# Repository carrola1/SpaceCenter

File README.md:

# Space_Center

## Lessons Learned
- Need to have GCC compiler optimization turned ON (optimize for size) for audio to work
-  tsl_user.h does not appear to be updating with Code Generation. Had to manually set Channel IOs definition (line 51)

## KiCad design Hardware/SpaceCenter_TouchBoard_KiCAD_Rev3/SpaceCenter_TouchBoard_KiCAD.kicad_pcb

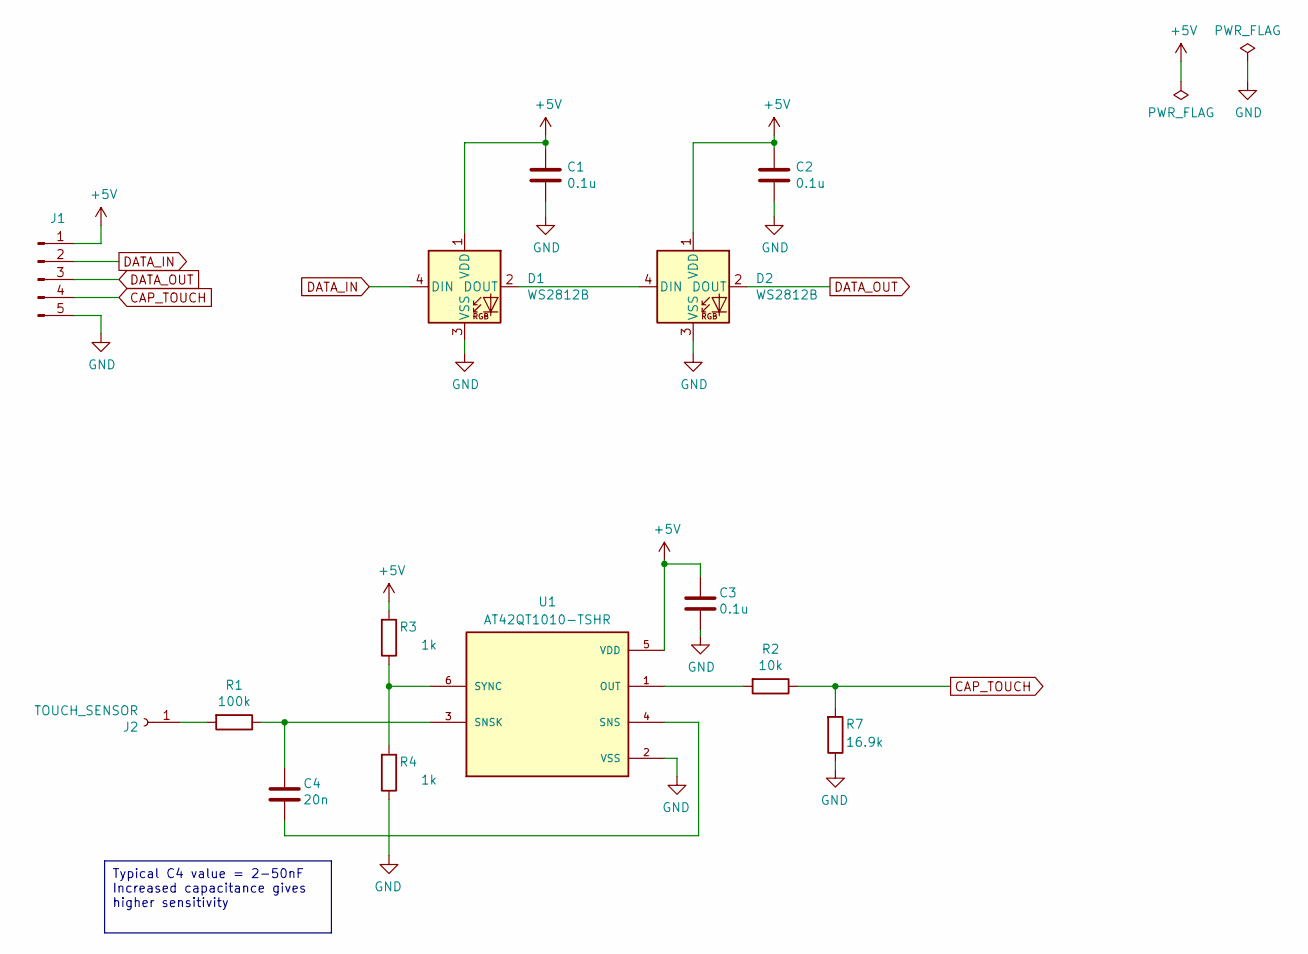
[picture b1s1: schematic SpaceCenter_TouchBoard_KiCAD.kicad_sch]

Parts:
C1, C2, C3: 0.1u; C_0402_1005Metric_Pad0.74x0.62mm_HandSolder
C4: 20n; C_0402_1005Metric_Pad0.74x0.62mm_HandSolder
D1, D2: WS2812B; LED_WS2812B_PLCC4_5.0x5.0mm_P3.2mm
J1: Conn_01x05_Male; JST_SH_BM05B-SRSS-TB_1x05-1MP_P1.00mm_Vertical
J2: TOUCH_SENSOR; SolderWirePad_1x01_SMD_5x10mm
R1: 100k; R_0402_1005Metric_Pad0.72x0.64mm_HandSolder
R2: 10k; R_0402_1005Metric_Pad0.72x0.64mm_HandSolder
R3, R4: 1k; R_0402_1005Metric_Pad0.72x0.64mm_HandSolder
R7: 16.9k; R_0402_1005Metric_Pad0.72x0.64mm_HandSolder
U1: AT42QT1010-TSHR; SOT95P270X145-6N; PARTREV DS40001946A

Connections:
+5V: C1.1, C2.1, C3.1, D1.1 (VDD), D2.1 (VDD), J1.1, R3.2, U1.5 (VDD); also elsewhere on the board
CAP_TOUCH: J1.4, R2.1, R7.2
DATA_IN: D1.4 (DIN), J1.2
DATA_OUT: D2.2 (DOUT), J1.3
GND: C1.2, C2.2, C3.2, D1.3 (VSS), D2.3 (VSS), J1.5, R4.1, R7.1, U1.2 (VSS); also elsewhere on the board
unnamed: D1.2 (DOUT), D2.4 (DIN)
unnamed: J2.1, R1.2
unnamed: R2.2, U1.1 (OUT)
unnamed: C4.2, U1.4 (SNS)
unnamed: C4.1, R1.1, U1.3 (SNSK)
unnamed: R3.1, R4.2, U1.6 (SYNC)

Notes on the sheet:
Typical C4 value = 2-50nF Increased capacitance gives higher sensitivity

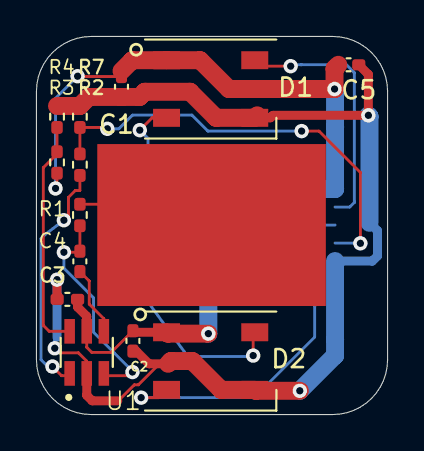
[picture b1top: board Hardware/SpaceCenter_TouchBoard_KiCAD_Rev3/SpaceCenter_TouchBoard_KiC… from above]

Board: 2 copper layers, 19.5 x 21.0 mm, 15 parts (1 on the bottom side), 11 nets.

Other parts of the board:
C5: 10u; C_0402_1005Metric_Pad0.74x0.62mm_HandSolder

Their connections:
+5V: C5.1; also elsewhere on the board
GND: C5.2; also elsewhere on the board

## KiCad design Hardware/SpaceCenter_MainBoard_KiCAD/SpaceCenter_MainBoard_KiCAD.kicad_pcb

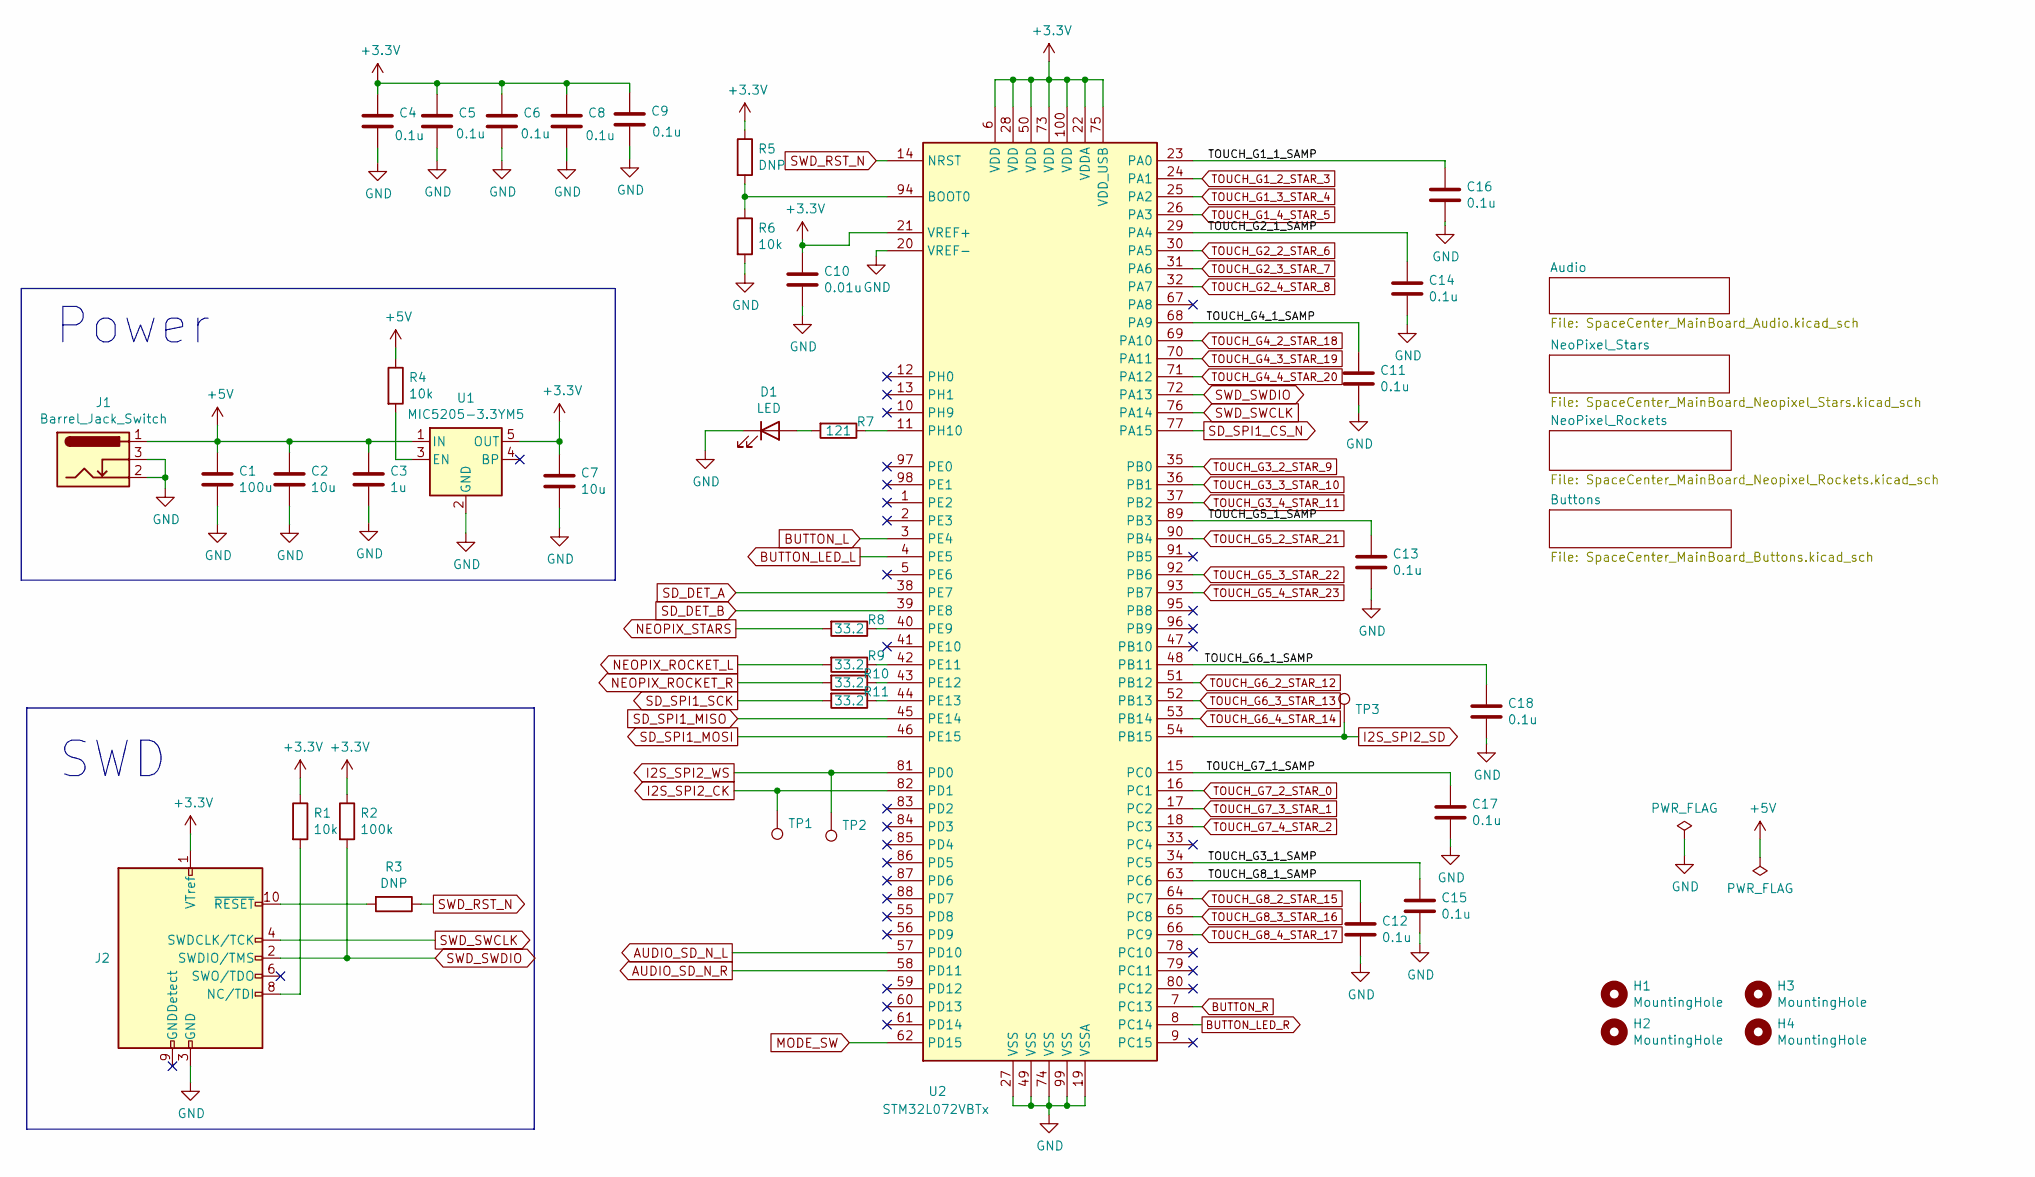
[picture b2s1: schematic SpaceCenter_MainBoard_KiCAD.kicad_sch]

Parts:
C1: 100u; C_1206_3216Metric_Pad1.42x1.75mm_HandSolder
C2, C7: 10u; C_0603_1608Metric_Pad1.05x0.95mm_HandSolder
C3: 1u; C_0603_1608Metric_Pad1.05x0.95mm_HandSolder
C4, C5, C6, C8, C9, C11, C12, C13, C14, C15, C16, C17, C18: 0.1u; C_0603_1608Metric_Pad1.05x0.95mm_HandSolder
C10: 0.01u; C_0603_1608Metric_Pad1.05x0.95mm_HandSolder
D1: LED; LED_0603_1608Metric_Pad1.05x0.95mm_HandSolder
H1, H2, H3, H4: MountingHole; MountingHole_3.2mm_M3
J1: Barrel_Jack_Switch; BarrelJack_CUI_PJ-102AH_Horizontal
J2: Conn_ARM_JTAG_SWD_10; PinHeader_2x05_P1.27mm_Vertical_SMD
R1, R4, R6: 10k; R_0603_1608Metric_Pad1.05x0.95mm_HandSolder
R2: 100k; R_0603_1608Metric_Pad1.05x0.95mm_HandSolder
R3, R5: DNP; R_0603_1608Metric_Pad1.05x0.95mm_HandSolder
R7: 121; R_0603_1608Metric_Pad1.05x0.95mm_HandSolder
R8, R9, R10, R11: 33.2; R_0603_1608Metric_Pad1.05x0.95mm_HandSolder
TP1, TP2, TP3: TestPoint; TestPoint_Keystone_5019_Minature
U1: MIC5205-3.3YM5; SOT-23-5
U2: STM32L072VBTx; LQFP-100_14x14mm_P0.5mm

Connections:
+3V3: C4.1, C5.1, C6.1, C7.1, C8.1, C9.1, C10.1, J2.1 (VTref), R1.1, R2.1, R5.1, U1.5 (OUT), U2.6 (VDD), U2.21 (VREF+), U2.22 (VDDA), U2.28 (VDD), U2.50 (VDD), U2.73 (VDD), U2.75 (VDD_USB), U2.100 (VDD); also elsewhere on the board
+5V: C1.1, C2.1, C3.1, J1.1, R4.1, U1.1 (IN); also elsewhere on the board
/TOUCH_G1_1_SAMP: C16.1, U2.23 (PA0)
/TOUCH_G2_1_SAMP: C14.1, U2.29 (PA4)
/TOUCH_G3_1_SAMP: C15.1, U2.34 (PC5)
/TOUCH_G4_1_SAMP: C11.1, U2.68 (PA9)
/TOUCH_G5_1_SAMP: C13.1, U2.89 (PB3)
/TOUCH_G6_1_SAMP: C18.1, U2.48 (PB11)
/TOUCH_G7_1_SAMP: C17.1, U2.15 (PC0)
/TOUCH_G8_1_SAMP: C12.1, U2.63 (PC6)
AUDIO_SD_N_L: U2.57 (PD10); also elsewhere on the board
AUDIO_SD_N_R: U2.58 (PD11); also elsewhere on the board
BUTTON_L: U2.3 (PE4); also elsewhere on the board
BUTTON_LED_L: U2.4 (PE5); also elsewhere on the board
BUTTON_LED_R: U2.8 (PC14); also elsewhere on the board
BUTTON_R: U2.7 (PC13); also elsewhere on the board
GND: C1.2, C2.2, C3.2, C4.2, C5.2, C6.2, C7.2, C8.2, C9.2, C10.2, C11.2, C12.2, C13.2, C14.2, C15.2, C16.2, C17.2, C18.2, D1.1 (K), J1.2, J1.3, J2.3 (GND), J2.5 (GND), R6.2, U1.2 (GND), U2.19 (VSSA), U2.20 (VREF-), U2.27 (VSS), U2.49 (VSS), U2.74 (VSS), U2.99 (VSS); also elsewhere on the board
I2S_SPI2_CK: TP1.1, U2.82 (PD1); also elsewhere on the board
I2S_SPI2_SD: TP3.1, U2.54 (PB15); also elsewhere on the board
I2S_SPI2_WS: TP2.1, U2.81 (PD0); also elsewhere on the board
MODE_SW: U2.62 (PD15); also elsewhere on the board
NEOPIX_ROCKET_L: R9.2; also elsewhere on the board
NEOPIX_ROCKET_R: R10.2; also elsewhere on the board
NEOPIX_STARS: R8.2; also elsewhere on the board
unnamed: D1.2 (A), R7.2
unnamed: J2.8 (NC/TDI), R1.2
unnamed: J2.10 (~RESET), R3.2
unnamed: R4.2, U1.3 (EN)
unnamed: R5.2, R6.1, U2.94 (BOOT0)
unnamed: R7.1, U2.11 (PH10)
unnamed: R8.1, U2.40 (PE9)
unnamed: R9.1, U2.42 (PE11)
unnamed: R10.1, U2.43 (PE12)
unnamed: R11.1, U2.44 (PE13)
SD_DET_A: U2.38 (PE7); also elsewhere on the board
SD_DET_B: U2.39 (PE8); also elsewhere on the board
SD_SPI1_CS_N: U2.77 (PA15); also elsewhere on the board
SD_SPI1_MISO: U2.45 (PE14); also elsewhere on the board
SD_SPI1_MOSI: U2.46 (PE15); also elsewhere on the board
SD_SPI1_SCK: R11.2; also elsewhere on the board
SWD_RST_N: R3.1, U2.14 (NRST)
SWD_SWCLK: J2.4 (SWDCLK/TCK), U2.76 (PA14)
SWD_SWDIO: J2.2 (SWDIO/TMS), R2.2, U2.72 (PA13)
TOUCH_G1_2_STAR_3: U2.24 (PA1); also elsewhere on the board
TOUCH_G1_3_STAR_4: U2.25 (PA2); also elsewhere on the board
TOUCH_G1_4_STAR_5: U2.26 (PA3); also elsewhere on the board
TOUCH_G2_2_STAR_6: U2.30 (PA5); also elsewhere on the board
TOUCH_G2_3_STAR_7: U2.31 (PA6); also elsewhere on the board
TOUCH_G2_4_STAR_8: U2.32 (PA7); also elsewhere on the board
TOUCH_G3_2_STAR_9: U2.35 (PB0); also elsewhere on the board
TOUCH_G3_3_STAR_10: U2.36 (PB1); also elsewhere on the board
TOUCH_G3_4_STAR_11: U2.37 (PB2); also elsewhere on the board
TOUCH_G4_2_STAR_18: U2.69 (PA10); also elsewhere on the board
TOUCH_G4_3_STAR_19: U2.70 (PA11); also elsewhere on the board
TOUCH_G4_4_STAR_20: U2.71 (PA12); also elsewhere on the board
TOUCH_G5_2_STAR_21: U2.90 (PB4); also elsewhere on the board
TOUCH_G5_3_STAR_22: U2.92 (PB6); also elsewhere on the board
TOUCH_G5_4_STAR_23: U2.93 (PB7); also elsewhere on the board
TOUCH_G6_2_STAR_12: U2.51 (PB12); also elsewhere on the board
TOUCH_G6_3_STAR_13: U2.52 (PB13); also elsewhere on the board
TOUCH_G6_4_STAR_14: U2.53 (PB14); also elsewhere on the board
TOUCH_G7_2_STAR_0: U2.16 (PC1); also elsewhere on the board
TOUCH_G7_3_STAR_1: U2.17 (PC2); also elsewhere on the board
TOUCH_G7_4_STAR_2: U2.18 (PC3); also elsewhere on the board
TOUCH_G8_2_STAR_15: U2.64 (PC7); also elsewhere on the board
TOUCH_G8_3_STAR_16: U2.65 (PC8); also elsewhere on the board
TOUCH_G8_4_STAR_17: U2.66 (PC9); also elsewhere on the board

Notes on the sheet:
Power
SWD

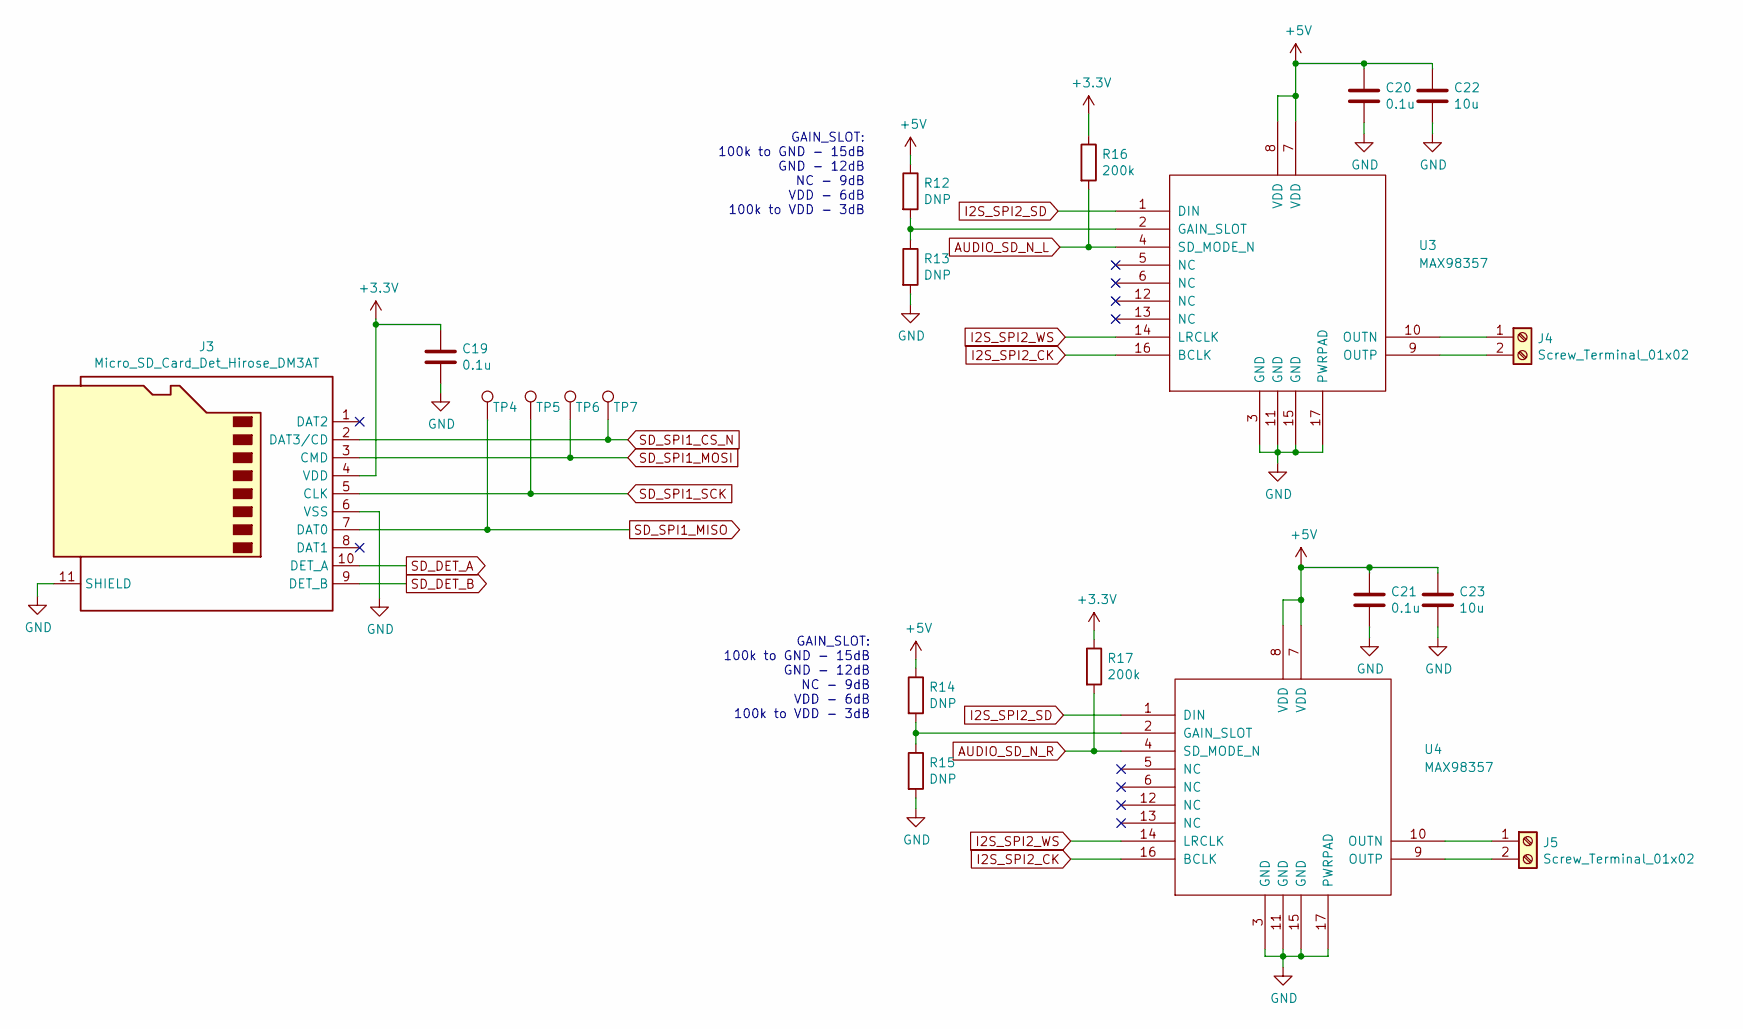
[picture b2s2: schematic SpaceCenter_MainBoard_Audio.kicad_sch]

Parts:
C19, C20, C21: 0.1u; C_0603_1608Metric_Pad1.05x0.95mm_HandSolder
C22, C23: 10u; C_0603_1608Metric_Pad1.05x0.95mm_HandSolder
J3: Micro_SD_Card_Det_Hirose_DM3AT; microSD_HC_Hirose_DM3AT-SF-PEJM5
J4, J5: Screw_Terminal_01x02; TerminalBlock_TE_282834-2_1x02_P2.54mm_Horizontal
R12, R13, R14, R15: DNP; R_0603_1608Metric_Pad1.05x0.95mm_HandSolder
R16, R17: 200k; R_0603_1608Metric_Pad1.05x0.95mm_HandSolder
TP4, TP5, TP6, TP7: TestPoint; TestPoint_Keystone_5019_Minature
U3, U4: MAX98357; QFN50P300X300X80-17N

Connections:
+3V3: C19.1, J3.4 (VDD), R16.1, R17.1; also elsewhere on the board
+5V: C20.1, C21.1, C22.1, C23.1, R12.1, R14.1, U3.7 (VDD), U3.8 (VDD), U4.7 (VDD), U4.8 (VDD); also elsewhere on the board
AUDIO_SD_N_L: R16.2, U3.4 (SD_MODE_N); also elsewhere on the board
AUDIO_SD_N_R: R17.2, U4.4 (SD_MODE_N); also elsewhere on the board
GND: C19.2, C20.2, C21.2, C22.2, C23.2, J3.6 (VSS), J3.11 (SHIELD), R13.2, R15.2, U3.3 (GND), U3.11 (GND), U3.15 (GND), U3.17 (PWRPAD), U4.3 (GND), U4.11 (GND), U4.15 (GND), U4.17 (PWRPAD); also elsewhere on the board
I2S_SPI2_CK: U3.16 (BCLK), U4.16 (BCLK); also elsewhere on the board
I2S_SPI2_SD: U3.1 (DIN), U4.1 (DIN); also elsewhere on the board
I2S_SPI2_WS: U3.14 (LRCLK), U4.14 (LRCLK); also elsewhere on the board
unnamed: J4.1, U3.10 (OUTN)
unnamed: J4.2, U3.9 (OUTP)
unnamed: J5.1, U4.10 (OUTN)
unnamed: J5.2, U4.9 (OUTP)
unnamed: R12.2, R13.1, U3.2 (GAIN_SLOT)
unnamed: R14.2, R15.1, U4.2 (GAIN_SLOT)
SD_DET_A: J3.10 (DET_A); also elsewhere on the board
SD_DET_B: J3.9 (DET_B); also elsewhere on the board
SD_SPI1_CS_N: J3.2 (DAT3/CD), TP7.1; also elsewhere on the board
SD_SPI1_MISO: J3.7 (DAT0), TP4.1; also elsewhere on the board
SD_SPI1_MOSI: J3.3 (CMD), TP6.1; also elsewhere on the board
SD_SPI1_SCK: J3.5 (CLK), TP5.1; also elsewhere on the board

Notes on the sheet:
GAIN_SLOT: 100k to GND - 15dB GND - 12dB NC - 9dB VDD - 6dB 100k to VDD - 3dB

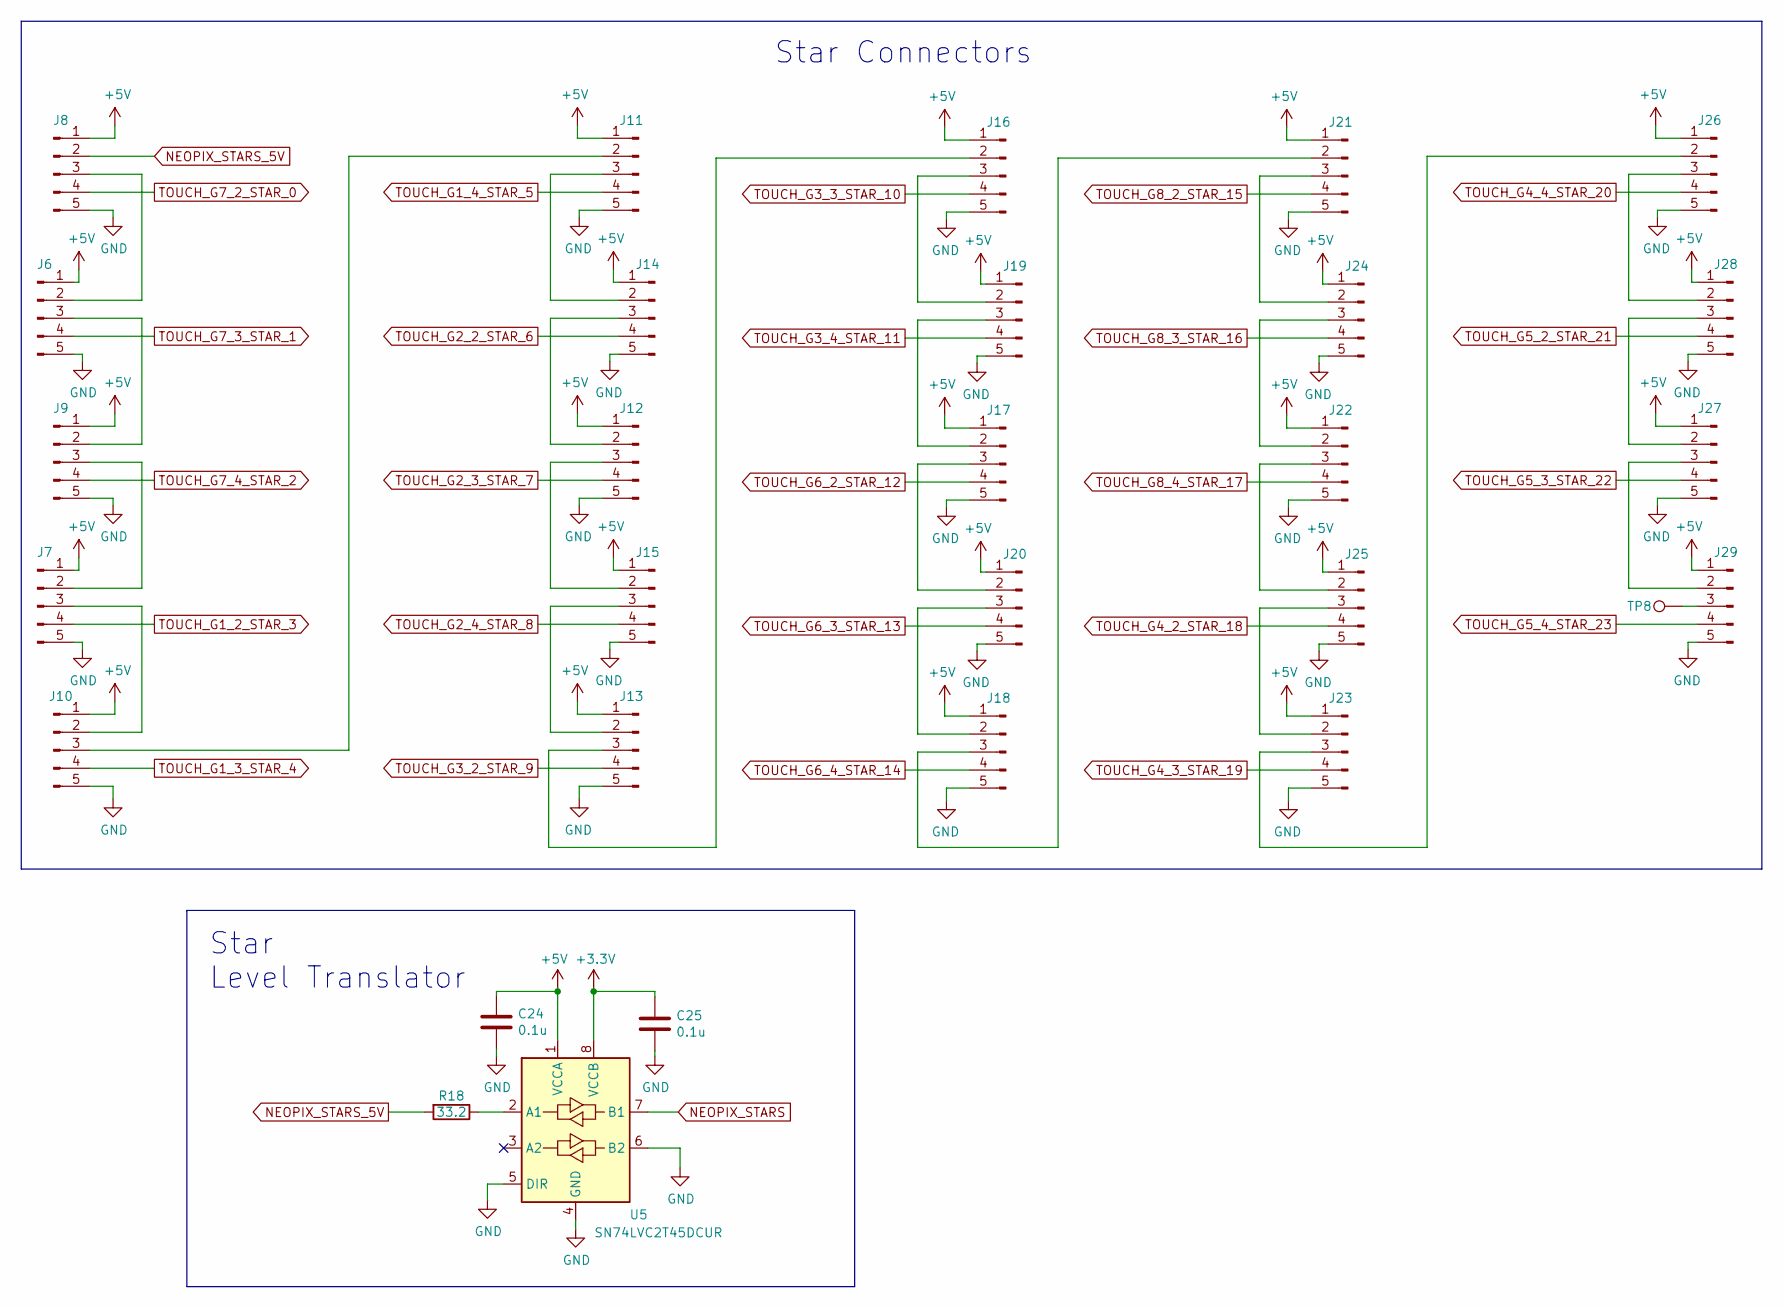
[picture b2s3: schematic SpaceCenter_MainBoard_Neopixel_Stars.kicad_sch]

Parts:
C24, C25: 0.1u; C_0603_1608Metric_Pad1.05x0.95mm_HandSolder
J6, J7, J8, J9, J10, J11, J12, J13, J14, J15, J16, J17, J18, J19, J20, J21, J22, J23, J24, J25, J26, J27, J28, J29: Conn_01x05_Male; JST_SH_BM05B-SRSS-TB_1x05-1MP_P1.00mm_Vertical
R18: 33.2; R_0603_1608Metric_Pad1.05x0.95mm_HandSolder
TP8: TestPoint; TestPoint_Keystone_5019_Minature
U5: SN74LVC2T45DCUR; VSSOP-8_2.4x2.1mm_P0.5mm

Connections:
+3V3: C25.1, U5.8 (VCCB); also elsewhere on the board
+5V: C24.1, J6.1, J7.1, J8.1, J9.1, J10.1, J11.1, J12.1, J13.1, J14.1, J15.1, J16.1, J17.1, J18.1, J19.1, J20.1, J21.1, J22.1, J23.1, J24.1, J25.1, J26.1, J27.1, J28.1, J29.1, U5.1 (VCCA); also elsewhere on the board
GND: C24.2, C25.2, J6.5, J7.5, J8.5, J9.5, J10.5, J11.5, J12.5, J13.5, J14.5, J15.5, J16.5, J17.5, J18.5, J19.5, J20.5, J21.5, J22.5, J23.5, J24.5, J25.5, J26.5, J27.5, J28.5, J29.5, U5.4 (GND), U5.5 (DIR), U5.6 (B2); also elsewhere on the board
NEOPIX_STARS: U5.7 (B1); also elsewhere on the board
NEOPIX_STARS_5V: J8.2, R18.2
unnamed: J6.2, J8.3
unnamed: J6.3, J9.2
unnamed: J7.2, J9.3
unnamed: J7.3, J10.2
unnamed: J10.3, J11.2
unnamed: J11.3, J14.2
unnamed: J12.2, J14.3
unnamed: J12.3, J15.2
unnamed: J13.2, J15.3
unnamed: J13.3, J16.2
unnamed: J16.3, J19.2
unnamed: J17.2, J19.3
unnamed: J17.3, J20.2
unnamed: J18.2, J20.3
unnamed: J18.3, J21.2
unnamed: J21.3, J24.2
unnamed: J22.2, J24.3
unnamed: J22.3, J25.2
unnamed: J23.2, J25.3
unnamed: J23.3, J26.2
unnamed: J26.3, J28.2
unnamed: J27.2, J28.3
unnamed: J27.3, J29.2
unnamed: J29.3, TP8.1
unnamed: R18.1, U5.2 (A1)
TOUCH_G1_2_STAR_3: J7.4; also elsewhere on the board
TOUCH_G1_3_STAR_4: J10.4; also elsewhere on the board
TOUCH_G1_4_STAR_5: J11.4; also elsewhere on the board
TOUCH_G2_2_STAR_6: J14.4; also elsewhere on the board
TOUCH_G2_3_STAR_7: J12.4; also elsewhere on the board
TOUCH_G2_4_STAR_8: J15.4; also elsewhere on the board
TOUCH_G3_2_STAR_9: J13.4; also elsewhere on the board
TOUCH_G3_3_STAR_10: J16.4; also elsewhere on the board
TOUCH_G3_4_STAR_11: J19.4; also elsewhere on the board
TOUCH_G4_2_STAR_18: J25.4; also elsewhere on the board
TOUCH_G4_3_STAR_19: J23.4; also elsewhere on the board
TOUCH_G4_4_STAR_20: J26.4; also elsewhere on the board
TOUCH_G5_2_STAR_21: J28.4; also elsewhere on the board
TOUCH_G5_3_STAR_22: J27.4; also elsewhere on the board
TOUCH_G5_4_STAR_23: J29.4; also elsewhere on the board
TOUCH_G6_2_STAR_12: J17.4; also elsewhere on the board
TOUCH_G6_3_STAR_13: J20.4; also elsewhere on the board
TOUCH_G6_4_STAR_14: J18.4; also elsewhere on the board
TOUCH_G7_2_STAR_0: J8.4; also elsewhere on the board
TOUCH_G7_3_STAR_1: J6.4; also elsewhere on the board
TOUCH_G7_4_STAR_2: J9.4; also elsewhere on the board
TOUCH_G8_2_STAR_15: J21.4; also elsewhere on the board
TOUCH_G8_3_STAR_16: J24.4; also elsewhere on the board
TOUCH_G8_4_STAR_17: J22.4; also elsewhere on the board

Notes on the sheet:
Star Level Translator
Star Connectors

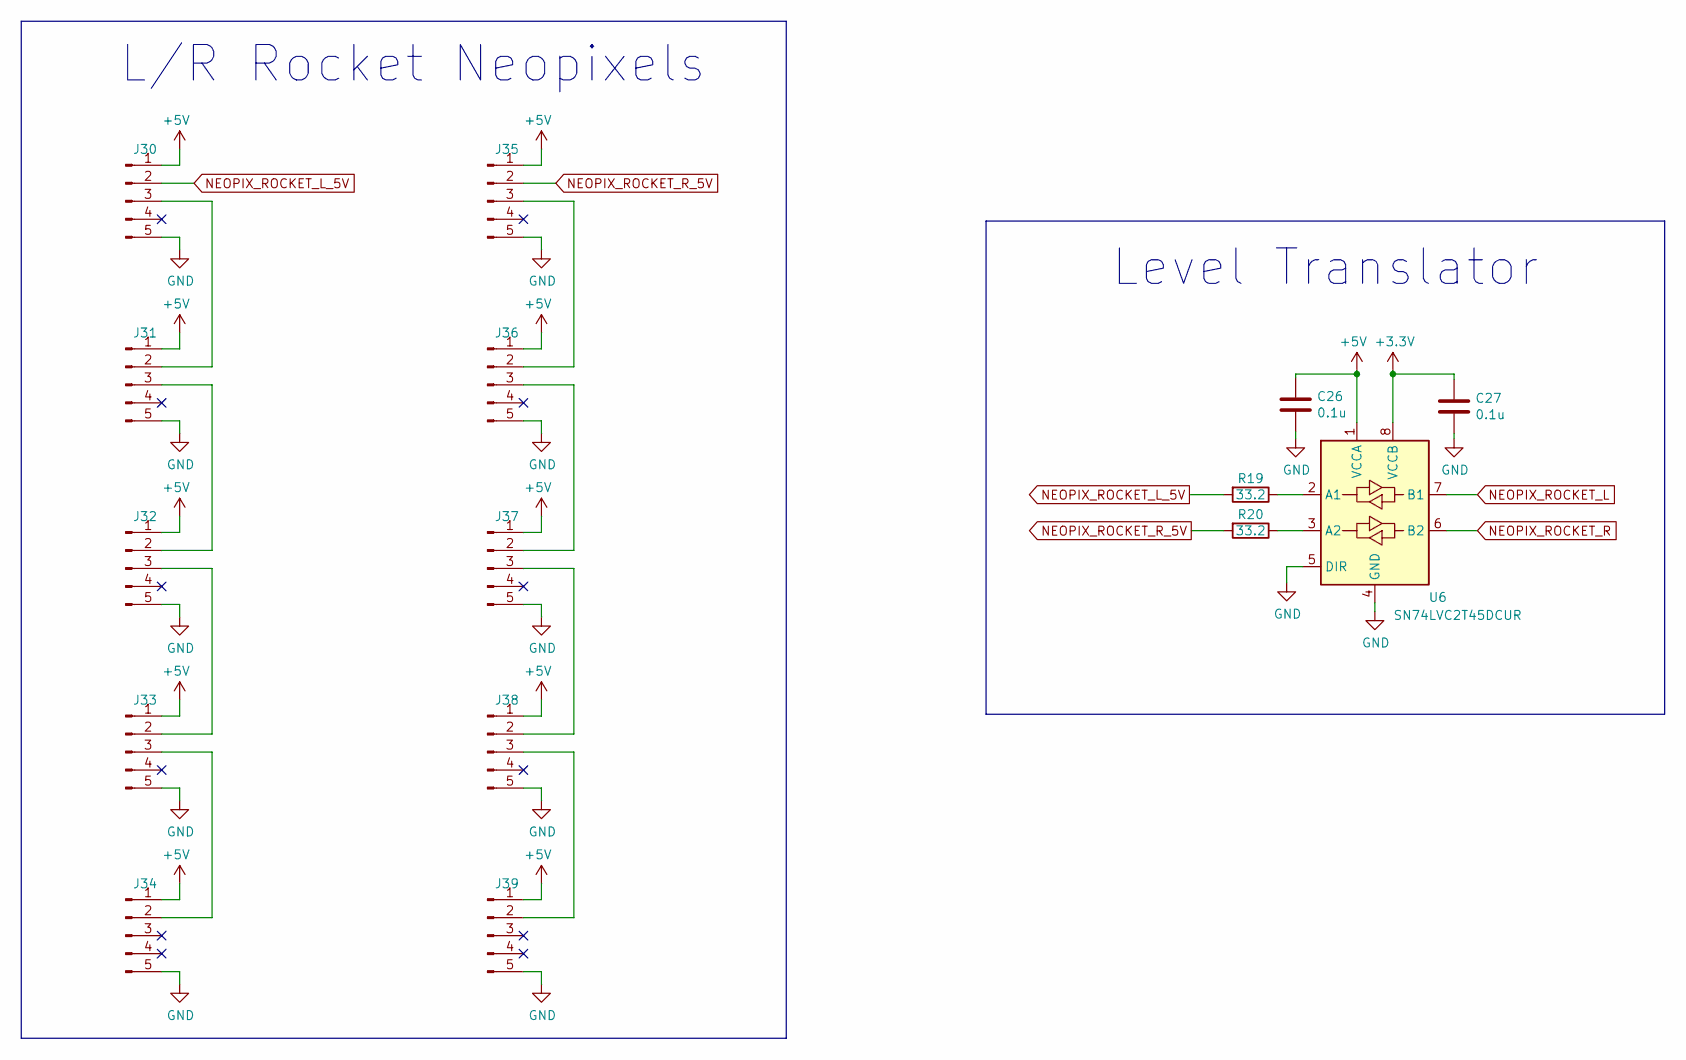
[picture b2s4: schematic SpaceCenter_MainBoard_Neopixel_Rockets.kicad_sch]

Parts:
C26, C27: 0.1u; C_0603_1608Metric_Pad1.05x0.95mm_HandSolder
J30, J31, J32, J33, J34, J35, J36, J37, J38, J39: Conn_01x05_Male; JST_SH_BM05B-SRSS-TB_1x05-1MP_P1.00mm_Vertical
R19, R20: 33.2; R_0603_1608Metric_Pad1.05x0.95mm_HandSolder
U6: SN74LVC2T45DCUR; VSSOP-8_2.4x2.1mm_P0.5mm

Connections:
+3V3: C27.1, U6.8 (VCCB); also elsewhere on the board
+5V: C26.1, J30.1, J31.1, J32.1, J33.1, J34.1, J35.1, J36.1, J37.1, J38.1, J39.1, U6.1 (VCCA); also elsewhere on the board
GND: C26.2, C27.2, J30.5, J31.5, J32.5, J33.5, J34.5, J35.5, J36.5, J37.5, J38.5, J39.5, U6.4 (GND), U6.5 (DIR); also elsewhere on the board
NEOPIX_ROCKET_L: U6.7 (B1); also elsewhere on the board
NEOPIX_ROCKET_L_5V: J30.2, R19.2
NEOPIX_ROCKET_R: U6.6 (B2); also elsewhere on the board
NEOPIX_ROCKET_R_5V: J35.2, R20.2
unnamed: J30.3, J31.2
unnamed: J31.3, J32.2
unnamed: J32.3, J33.2
unnamed: J33.3, J34.2
unnamed: J35.3, J36.2
unnamed: J36.3, J37.2
unnamed: J37.3, J38.2
unnamed: J38.3, J39.2
unnamed: R19.1, U6.2 (A1)
unnamed: R20.1, U6.3 (A2)

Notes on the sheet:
Level Translator
L/R Rocket Neopixels

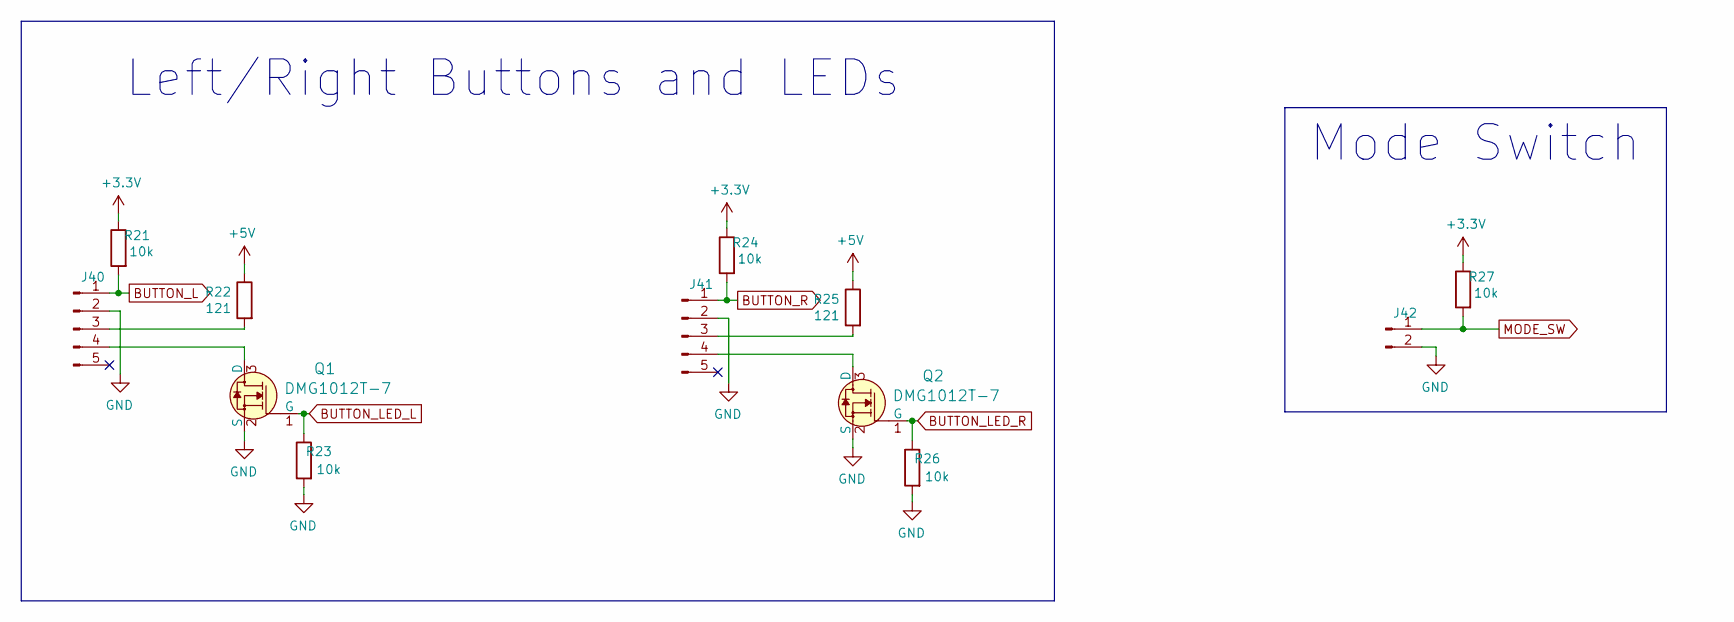
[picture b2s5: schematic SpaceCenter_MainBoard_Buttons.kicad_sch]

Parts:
J40, J41: Conn_01x05_Male; JST_SH_BM05B-SRSS-TB_1x05-1MP_P1.00mm_Vertical
J42: Conn_01x02_Male; PinHeader_1x02_P2.54mm_Vertical
Q1, Q2: DMG1012T-7; SOT-523; MPN DMG1012T-7; Digi-Key_PN DMG1012T-7DICT-ND
R21, R23, R24, R26, R27: 10k; R_0603_1608Metric_Pad1.05x0.95mm_HandSolder
R22, R25: 121; R_0603_1608Metric_Pad1.05x0.95mm_HandSolder

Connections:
+3V3: R21.1, R24.1, R27.1; also elsewhere on the board
+5V: R22.1, R25.1; also elsewhere on the board
BUTTON_L: J40.1, R21.2; also elsewhere on the board
BUTTON_LED_L: Q1.1 (G), R23.1; also elsewhere on the board
BUTTON_LED_R: Q2.1 (G), R26.1; also elsewhere on the board
BUTTON_R: J41.1, R24.2; also elsewhere on the board
GND: J40.2, J41.2, J42.2, Q1.2 (S), Q2.2 (S), R23.2, R26.2; also elsewhere on the board
MODE_SW: J42.1, R27.2; also elsewhere on the board
unnamed: J40.3, R22.2
unnamed: J40.4, Q1.3 (D)
unnamed: J41.3, R25.2
unnamed: J41.4, Q2.3 (D)

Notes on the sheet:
Mode Switch
Left/Right Buttons and LEDs

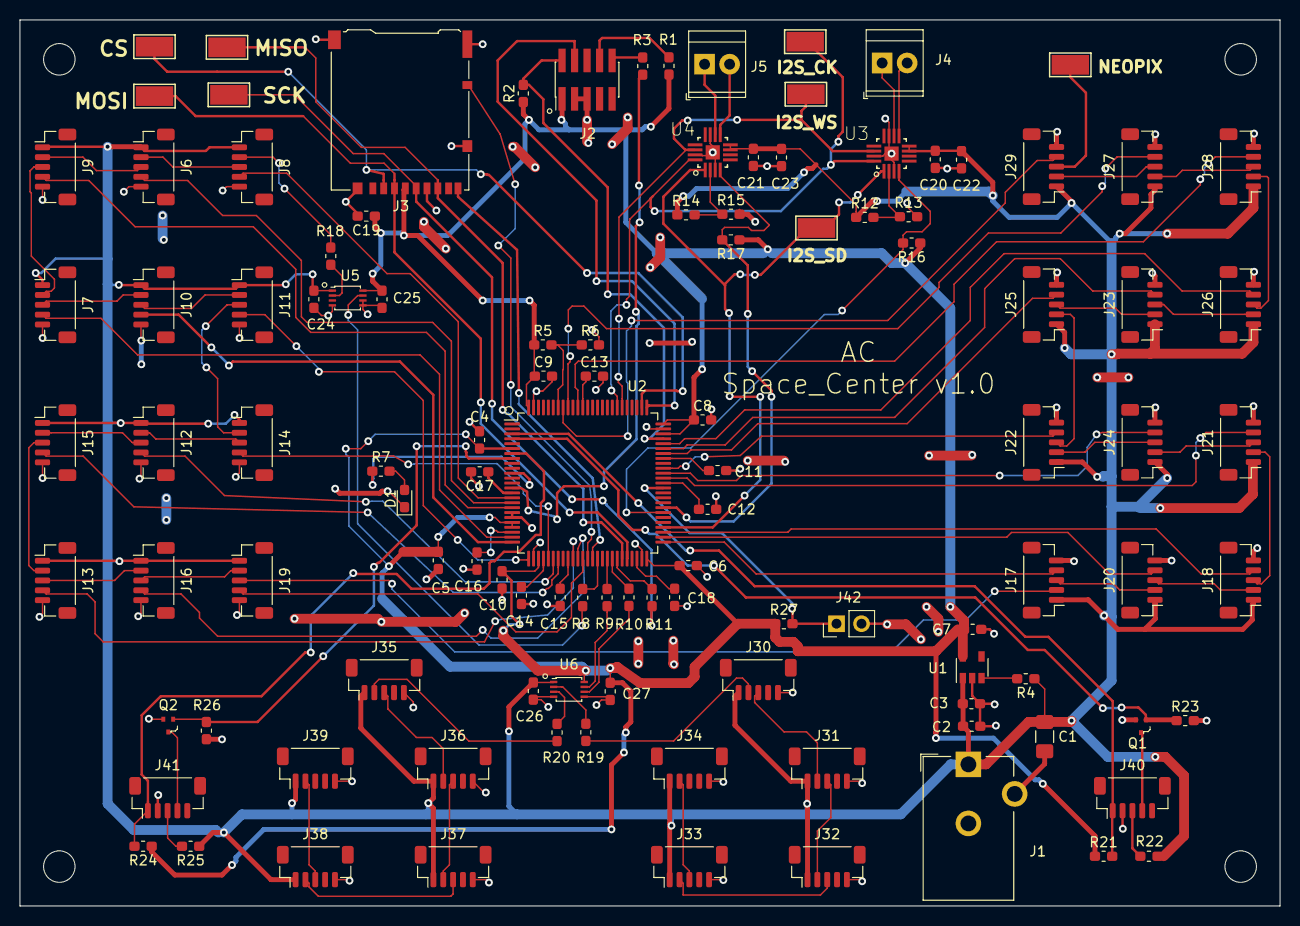
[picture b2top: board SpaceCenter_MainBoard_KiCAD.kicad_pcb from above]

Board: 2 copper layers, 128.0 x 90.0 mm, 117 parts (0 on the bottom side), 115 nets.

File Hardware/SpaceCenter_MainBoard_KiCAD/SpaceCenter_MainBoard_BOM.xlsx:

Item | Ref Des | Qty | Part # | Digi-key Part # | Value/Description | Package | Type | Instructions | DigiKey Cost (Each) | DigiKey Cost (Total)
1 | J6,J7,J8,J9,J10,J11,J12,J13,J14,J15,J16,J17,J18,J19,J20,J21,J22,J23,J24,J25,J26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 | 36 | DO NOT POPULATE | DO NOT POPULATE | Conn_01x05_Male | JST_SH_BM05B-SRSS-TB_1x05-1MP_P1.00mm_Vertical | SMD | DO NOT POPULATE | 0.73 | 26.28
2 | C1 | 1 | Basic | N/A | Ceramic 100u, 6.3V +/-20% or better | C_1206_3216Metric | SMD |  | 0.1 | 0.1
3 | C2,C7,C22,C23 | 4 | Basic | N/A | Ceramic 10u, 6.3V +/-20% or better | C_0603_1608Metric | SMD |  | 0.1 | 0.4
4 | C3 | 1 | Basic | N/A | Ceramic 1u, 6.3V +/-20% or better | C_0603_1608Metric | SMD |  | 0.1 | 0.1
5 | C4,C5,C6,C8,C9,C11,C12,C13,C14,C15,C16,C17,C18, C19,C20,C21,C24,C25,C26,C27 | 20 | Basic | N/A | Ceramic 0.1u 50V +/-10% or better | C_0603_1608Metric | SMD |  | 0.1 | 2
6 | C10 | 1 | Basic | N/A | Ceramic 0.01u 50V +/-10% or better | C_0603_1608Metric | SMD |  | 0.1 | 0.1
7 | D1 | 1 | LTST-C191KGKT | 160-1446-1-ND | LED | LED_0603_1608Metric | SMD |  | 0.26 | 0.26
8 | H1,H2,H3,H4 | 4 | N/A | N/A | MountingHole | MountingHole_3.2mm_M3 | SMD |  | N/A | N/A
9 | J1 | 1 | PJ-102AH | CP-102AH-ND | Barrel_Jack_Switch | BarrelJack_CUI_PJ-102AH_Horizontal | SMD |  | 0.76 | 0.76
10 | J2 | 1 | 20021121-00010C4LF | 609-3695-1-ND | Conn_ARM_JTAG_SWD_10 | PinHeader_2x05_P1.27mm_Vertical_SMD | SMD |  | 0.83 | 0.83
11 | J3 | 1 | DM3AT-SF-PEJM5 | HR1964CT-ND | Micro_SD_Card_Det_Hirose_DM3AT | microSD_HC_Hirose_DM3AT-SF-PEJM5 | SMD |  | 2.5 | 2.5
12 | J4,J5 | 2 | 282834-2 | A98333-ND | Screw_Terminal_01x02 | TerminalBlock_TE_282834-2_1x02_P2.54mm_Horizontal | THT | Screw terminals face out (toward edge of PCB) | 1.27 | 2.54
13 | J42 | 1 | 61300211121 | 732-5315-ND | Conn_01x02_Male | PinHeader_1x02_P2.54mm_Vertical | THT | Equivalent part # is acceptable | 0.13 | 0.13
14 | Q1,Q2 | 2 | DMG1012T-7 | DMG1012T-7DICT-ND | MOSFET N-CH 20V 630MA | SOT-523 | SMD |  | 0.31 | 0.62
15 | R1,R4,R6,R21,R23,R24,R26,R27 | 8 | Basic | N/A | 10k | R_0603_1608Metric | SMD |  | 0.1 | 0.8
16 | R2 | 1 | Basic | N/A | 100k | R_0603_1608Metric | SMD |  | 0.1 | 0.1
17 | R3,R5,R12,R13,R14,R15 | 6 | DO NOT POPULATE | N/A | DNP | R_0603_1608Metric | SMD | DO NOT POPULATE | 0.1 | 0.60000000000000009
18 | R7,R22,R25 | 3 | Basic | N/A | 121 | R_0603_1608Metric | SMD |  | 0.1 | 0.30000000000000004
19 | R8,R9,R10,R11,R18,R19,R20 | 7 | Basic | N/A | 33.2 | R_0603_1608Metric | SMD |  | 0.1 | 0.70000000000000007
20 | R16,R17 | 2 | Basic | N/A | 200k | R_0603_1608Metric | SMD |  | 0.1 | 0.2
21 | TP1,TP2,TP3,TP4,TP5,TP6,TP7,TP8 | 8 | DO NOT POPULATE | N/A | TestPoint | TestPoint_Keystone_5019_Minature | SMD | DO NOT POPULATE | 0.1 | 0.8
22 | U1 | 1 | MIC5205-3.3YM5-TR | 576-1259-1-ND | IC REG LINEAR 3.3V 150MA | SOT-23-5 | SMD |  | 0.42 | 0.42
23 | U2 | 1 | STM32L072VBT6 | 497-18582-ND | IC MCU 32BIT 128KB FLASH | LQFP-100_14x14mm_P0.5mm | SMD |  | 6.03 | 6.03
24 | U3,U4 | 2 | MAX98357AETE+T | MAX98357AETE+TCT-ND | IC AMP CLASS D MONO 3.2W | QFN50P300X300X80-17N | SMD |  | 2.44 | 4.88
25 | U5,U6 | 2 | SN74LVC2T45DCUR | 296-17014-1-ND | SN74LVC2T45DCUR | VSSOP-8_2.4x2.1mm_P0.5mm | SMD |  | 0.63 | 1.26
 |  |  |  |  |  |  |  |  |  | 52.710000000000008
 |  | 60

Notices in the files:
parts and their libraries:
Copyright 2021 Accelerated Designs. All rights reserved.
